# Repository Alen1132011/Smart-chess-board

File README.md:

# Smart Chess Board

A physical chess board that can detect the position of chess pieces in real time using Hall effect sensors and provide visual feedback through RGB LEDs.

The project combines custom electronics, firmware and a 3D printed enclosure to create a chess board that can understand what is happening on the board without using mechanical switches.

## Budget & SMT Notes

- **Shipping:** Selected the cheapest available shipping method to Bosnia and Herzegovina ($71.75).
- **SMT Assembly:** I attempted to use Economic SMT Assembly to minimize costs, but JLCPCB automatically forces a switch to **Standard SMT Assembly** when incorporating WS2812B addressable LEDs.
- **Self-Funded Components:** To keep the requested grant minimal, I will personally cover all additional hardware costs (ESP32 controller board, magnets, and 3D printing materials for the enclosure).

## Current Status

The PCB design is complete and the first board is being prepared for production and assembly.

The project is still in development. Some features described below are planned and will be added as the hardware and firmware develop.

Once I assemble and test the first board, I will add more information to this repository, including photos, test results and a much more detailed assembly guide.

## Features

* Real-time piece detection using Hall effect sensors
* 128 Hall effect sensors
* RGB lighting under the chess squares
* Custom PCB designed specifically for the board
* Magnetic chess pieces using neodymium magnets
* Firmware developed for the board
* Planned Stockfish integration
* Planned connection to online chess platforms

## How It Works

Each chess piece has a small magnet in its base. Hall effect sensors placed underneath the board detect the magnetic field and determine whether a piece is present on a square.

The board uses 128 sensors connected through 74HC165 shift registers. This allows the microcontroller to read a large number of sensors without requiring a separate input pin for every sensor.

RGB LEDs are placed underneath the squares and can be used to show things such as possible moves, selected pieces, warnings and other information.

The main idea is to keep the playing surface completely clean while putting all of the electronics underneath it.

## Hardware

The main components currently used in the design are:

* Custom PCB designed in KiCad
* 128x HAL2041SO Hall effect sensors
* 16x 74HC165 shift registers
* SK6812 / WS2812B RGB LEDs
* 100nF capacitors
* 10kΩ and 330Ω resistors
* Chess pieces with neodymium magnets

The exact components and values may change after the first prototype is assembled and tested.

## Repository Structure

```text
CAD/              3D models and enclosure design
Firmware/         Board firmware
PCB/              KiCad PCB design files
Production/       Manufacturing and production files
Smart chess board Additional project files
README.md         Project documentation
```

## Assembly

The first version of the board has not been fully assembled yet, so the complete assembly guide is not available at the moment.

After I build the first board, I will add a detailed guide covering:

* PCB assembly
* Hall sensor placement
* LED installation
* Wiring and power
* Magnet placement in the chess pieces
* Firmware installation
* Initial testing and calibration
* Common problems and fixes

I want the guide to be based on the actual first build rather than documenting steps that have not been tested yet.

## Future Plans

The project is still being developed, and more features will be added after the first working board is finished.

Some of the planned improvements include:

* Stockfish integration
* Better move detection and validation
* More RGB lighting effects
* Online chess integration
* Calibration tools
* Improved enclosure
* More detailed documentation

The first assembled board will be an important milestone because it will show which parts of the current design work as expected and which parts need to be improved.

## Libraries and Tools

* KiCad
* PlatformIO
* FastLED
* Stockfish
  
 ## Project Renders & Schematics

## Project Status

PCB design: Complete
CAD design: In progress
Firmware: In progress
First board assembly: Upcoming
Detailed assembly guide: Coming after the first build

This project is being developed step by step. The documentation will be updated as the physical board is built, tested and improved.

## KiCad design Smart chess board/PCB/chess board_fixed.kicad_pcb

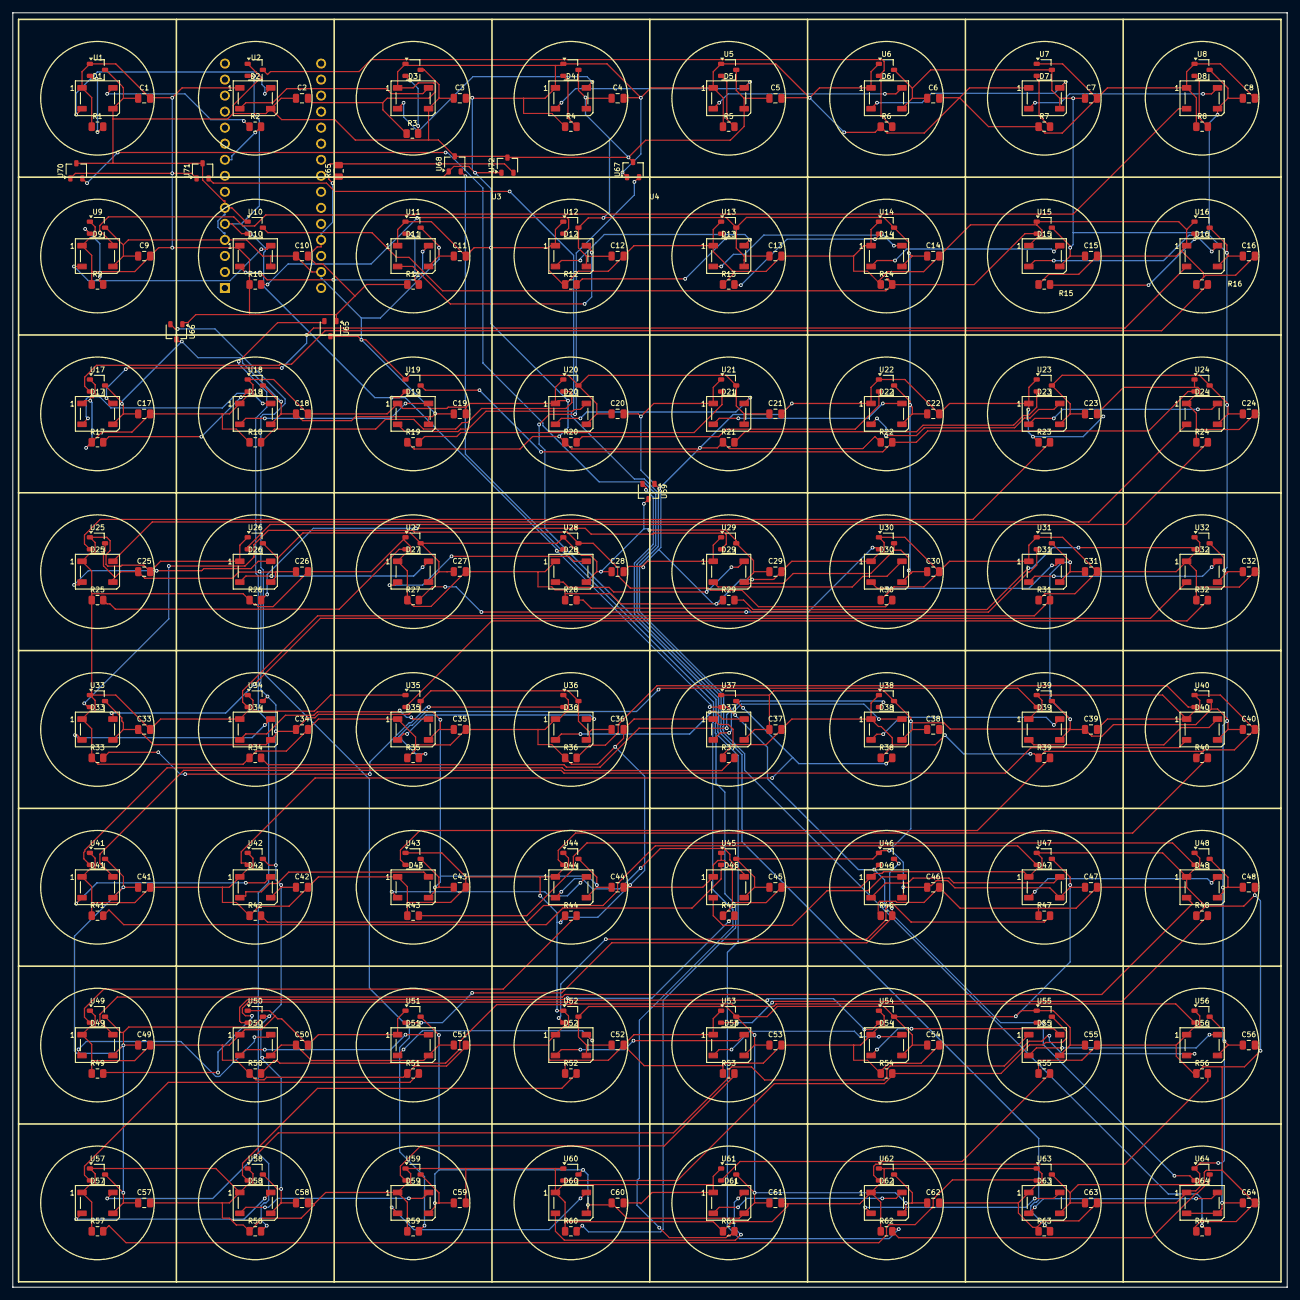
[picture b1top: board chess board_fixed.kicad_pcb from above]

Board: 2 copper layers, 201.9 x 201.9 mm, 266 parts (1 on the bottom side), 132 nets.

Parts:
A1: Arduino_Nano_Every; Arduino_Nano
C1, C2, C3, C4, C5, C6, C7, C8, C9, C10, C11, C12, C13, C14, C15, C16, C17, C18, C19, C20, C21, C22, C23, C24, C25, C26, C27, C28, C29, C30, C31, C32, C33, C34, C35, C36, C37, C38, C39, C40, C41, C42, C43, C44, C45, C46, C47, C48, C49, C50, C51, C52, C53, C54, C55, C56, C57, C58, C59, C60, C61, C62, C63, C64: 100nF; C_0805_2012Metric
D1, D2, D3, D4, D5, D6, D7, D8, D9, D10, D11, D12, D13, D14, D15, D16, D17, D18, D19, D20, D21, D22, D23, D24, D25, D26, D27, D28, D29, D30, D31, D32, D33, D34, D35, D36, D37, D38, D39, D40, D41, D42, D43, D44, D45, D46, D47, D48, D49, D50, D51, D52, D53, D54, D55, D56, D57, D58, D59, D60, D61, D62, D63, D64: WS2812B; LED_WS2812B_PLCC4_5.0x5.0mm_P3.2mm
R1, R3, R4, R5, R6, R7, R8, R9, R10, R11, R12, R13, R14, R15, R16, R17, R18, R19, R20, R21, R22, R23, R24, R25, R26, R27, R28, R29, R30, R31, R32, R33, R34, R35, R36, R37, R38, R39, R40, R41, R42, R43, R44, R45, R46, R47, R48, R49, R50, R51, R52, R53, R54, R55, R56, R57, R58, R59, R60, R61, R62, R63, R64, R65: 10k; R_0805_2012Metric
R2: 330Ω; R_0805_2012Metric
U1, U3, U4, U5, U6, U7, U8, U9, U11, U12, U13, U14, U15, U16, U17, U18, U20, U21, U22, U23, U24, U25, U26, U27, U29, U30, U31, U32, U33, U34, U35, U36, U38, U39, U40, U41, U42, U43, U44, U45, U47, U48, U49, U50, U51, U52, U53, U54, U56, U57, U58, U59, U60, U61, U62, U63, U65, U66, U67, U68, U69, U70, U71, U72: A1104xLH; SOT-23W
U2, U10, U19, U28, U37, U46, U55, U64: 74HC165; SOT-23W

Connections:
+5V: A1.27 (+5V), C1.2, C2.2, C3.2, C4.2, C5.2, C6.2, C7.2, C8.2, C9.2, C10.2, C11.2, C12.2, C13.2, C14.2, C15.2, C16.2, C17.2, C18.2, C19.2, C20.2, C21.2, C22.2, C23.2, C24.2, C25.2, C26.2, C27.2, C28.2, C29.2, C30.2, C31.2, C32.2, C33.2, C34.2, C35.2, C36.2, C37.2, C38.2, C39.2, C40.2, C41.2, C42.2, C43.2, C44.2, C45.2, C46.2, C47.2, C48.2, C49.2, C50.2, C51.2, C52.2, C53.2, C54.2, C55.2, C56.2, C57.2, C58.2, C59.2, C60.2, C61.2, C62.2, C63.2, C64.2, D1.1 (VDD), D2.1 (VDD), D3.1 (VDD), D4.1 (VDD), D5.1 (VDD), D6.1 (VDD), D7.1 (VDD), D8.1 (VDD), D9.1 (VDD), D10.1 (VDD), D11.1 (VDD), D12.1 (VDD), D13.1 (VDD), D14.1 (VDD), D15.1 (VDD), D16.1 (VDD), D17.1 (VDD), D18.1 (VDD), D19.1 (VDD), D20.1 (VDD), D21.1 (VDD), D22.1 (VDD), D23.1 (VDD), D24.1 (VDD), D25.1 (VDD), D26.1 (VDD), D27.1 (VDD), D28.1 (VDD), D29.1 (VDD), D30.1 (VDD), D31.1 (VDD), D32.1 (VDD), D33.1 (VDD), D34.1 (VDD), D35.1 (VDD), D36.1 (VDD), D37.1 (VDD), D38.1 (VDD), D39.1 (VDD), D40.1 (VDD), D41.1 (VDD), D42.1 (VDD), D43.1 (VDD), D44.1 (VDD), D45.1 (VDD), D46.1 (VDD), D47.1 (VDD), D48.1 (VDD), D49.1 (VDD), D50.1 (VDD), D51.1 (VDD), D52.1 (VDD), D53.1 (VDD), D54.1 (VDD), D55.1 (VDD), D56.1 (VDD), D57.1 (VDD), D58.1 (VDD), D59.1 (VDD), D60.1 (VDD), D61.1 (VDD), D62.1 (VDD), D63.1 (VDD), D64.1 (VDD), R1.1, R3.1, R4.1, R5.1, R6.1, R7.1, R8.1, R9.1, R10.1, R11.1, R12.1, R13.1, R14.1, R15.1, R16.1, R17.1, R18.1, R19.1, R20.1, R21.1, R22.1, R23.1, R24.1, R25.1, R26.1, R27.1, R28.1, R29.1, R30.1, R31.1, R32.1, R33.1, R34.1, R35.1, R36.1, R37.1, R38.1, R39.1, R40.1, R41.1, R42.1, R43.1, R44.1, R45.1, R46.1, R47.1, R48.1, R49.1, R50.1, R51.1, R52.1, R53.1, R54.1, R55.1, R56.1, R57.1, R58.1, R59.1, R60.1, R61.1, R62.1, R63.1, R64.1, R65.1, U1.1 (V_{CC}), U3.1 (V_{CC}), U4.1 (V_{CC}), U5.1 (V_{CC}), U6.1 (V_{CC}), U7.1 (V_{CC}), U8.1 (V_{CC}), U9.1 (V_{CC}), U11.1 (V_{CC}), U12.1 (V_{CC}), U13.1 (V_{CC}), U14.1 (V_{CC}), U15.1 (V_{CC}), U16.1 (V_{CC}), U17.1 (V_{CC}), U18.1 (V_{CC}), U20.1 (V_{CC}), U21.1 (V_{CC}), U22.1 (V_{CC}), U23.1 (V_{CC}), U24.1 (V_{CC}), U25.1 (V_{CC}), U26.1 (V_{CC}), U27.1 (V_{CC}), U29.1 (V_{CC}), U30.1 (V_{CC}), U31.1 (V_{CC}), U32.1 (V_{CC}), U33.1 (V_{CC}), U34.1 (V_{CC}), U35.1 (V_{CC}), U36.1 (V_{CC}), U38.1 (V_{CC}), U39.1 (V_{CC}), U40.1 (V_{CC}), U41.1 (V_{CC}), U42.1 (V_{CC}), U43.1 (V_{CC}), U44.1 (V_{CC}), U45.1 (V_{CC}), U47.1 (V_{CC}), U48.1 (V_{CC}), U49.1 (V_{CC}), U50.1 (V_{CC}), U51.1 (V_{CC}), U52.1 (V_{CC}), U53.1 (V_{CC}), U54.1 (V_{CC}), U56.1 (V_{CC}), U57.1 (V_{CC}), U58.1 (V_{CC}), U59.1 (V_{CC}), U60.1 (V_{CC}), U61.1 (V_{CC}), U62.1 (V_{CC}), U63.1 (V_{CC}), U65.1 (V_{CC}), U66.1 (V_{CC}), U67.1 (V_{CC}), U68.1 (V_{CC}), U69.1 (V_{CC}), U70.1 (V_{CC}), U71.1 (V_{CC}), U72.1 (V_{CC})
/S0: R1.2, U1.2 (V_{OUT})
/S1: R3.2, U3.2 (V_{OUT})
/S2: R4.2, U4.2 (V_{OUT})
/S3: R5.2, U5.2 (V_{OUT})
/S4: R6.2, U2.3 (D4), U6.2 (V_{OUT})
/S5: R7.2, U7.2 (V_{OUT})
/S6: R8.2, U8.2 (V_{OUT})
/S7: R9.2, U9.2 (V_{OUT})
/S8: R11.2, U11.2 (V_{OUT})
/S9: R10.2, U12.2 (V_{OUT})
/S10: R12.2, U13.2 (V_{OUT})
/S11: R13.2, U14.2 (V_{OUT})
/S12: R14.2, U10.3 (D4), U15.2 (V_{OUT})
/S13: R15.2, U16.2 (V_{OUT})
/S14: R16.2, U17.2 (V_{OUT})
/S15: R17.2, U18.2 (V_{OUT})
/S16: R18.2, U20.2 (V_{OUT})
/S17: R19.2, U21.2 (V_{OUT})
/S18: R20.2, U22.2 (V_{OUT})
/S19: R21.2, U23.2 (V_{OUT})
/S20: R22.2, U19.3 (D4), U24.2 (V_{OUT})
/S21: R23.2, U25.2 (V_{OUT})
/S22: R24.2, U26.2 (V_{OUT})
/S23: R25.2, U27.2 (V_{OUT})
/S24: R26.2, U29.2 (V_{OUT})
/S25: R27.2, U30.2 (V_{OUT})
/S26: R28.2, U31.2 (V_{OUT})
/S27: R29.2, U32.2 (V_{OUT})
/S28: R30.2, U28.3 (D4), U33.2 (V_{OUT})
/S29: R31.2, U34.2 (V_{OUT})
/S30: R32.2, U35.2 (V_{OUT})
/S31: R33.2, U36.2 (V_{OUT})
/S32: R34.2, U38.2 (V_{OUT})
/S33: R35.2, U39.2 (V_{OUT})
/S34: R36.2, U40.2 (V_{OUT})
/S35: R37.2, U41.2 (V_{OUT})
/S36: R38.2, U37.3 (D4), U42.2 (V_{OUT})
/S37: R39.2, U43.2 (V_{OUT})
/S38: R40.2, U44.2 (V_{OUT})
/S39: R41.2, U45.2 (V_{OUT})
/S40: R42.2, U47.2 (V_{OUT})
/S41: R43.2, U48.2 (V_{OUT})
/S42: R44.2, U49.2 (V_{OUT})
/S43: R45.2, U50.2 (V_{OUT})
/S44: R46.2, U46.3 (D4), U51.2 (V_{OUT})
/S45: R47.2, U52.2 (V_{OUT})
/S46: R48.2, U53.2 (V_{OUT})
/S47: R49.2, U54.2 (V_{OUT})
/S48: R50.2, U56.2 (V_{OUT})
/S49: R51.2, U57.2 (V_{OUT})
/S50: R52.2, U58.2 (V_{OUT})
/S51: R53.2, U59.2 (V_{OUT})
/S52: R54.2, U55.3 (D4), U60.2 (V_{OUT})
/S53: R55.2, U61.2 (V_{OUT})
/S54: R56.2, U62.2 (V_{OUT})
/S55: R57.2, U63.2 (V_{OUT})
/S56: R58.2, U65.2 (V_{OUT})
/S57: R59.2, U66.2 (V_{OUT})
/S58: R60.2, U67.2 (V_{OUT})
/S59: R61.2, U68.2 (V_{OUT})
/S60: R62.2, U64.3 (D4), U69.2 (V_{OUT})
/S61: R63.2, U70.2 (V_{OUT})
/S62: R64.2, U71.2 (V_{OUT})
/S63: R65.2, U72.2 (V_{OUT})
GND: A1.4 (GND), A1.6 (D3), A1.29 (GND), C1.1, C2.1, C3.1, C4.1, C5.1, C6.1, C7.1, C8.1, C9.1, C10.1, C11.1, C12.1, C13.1, C14.1, C15.1, C16.1, C17.1, C18.1, C19.1, C20.1, C21.1, C22.1, C23.1, C24.1, C25.1, C26.1, C27.1, C28.1, C29.1, C30.1, C31.1, C32.1, C33.1, C34.1, C35.1, C36.1, C37.1, C38.1, C39.1, C40.1, C41.1, C42.1, C43.1, C44.1, C45.1, C46.1, C47.1, C48.1, C49.1, C50.1, C51.1, C52.1, C53.1, C54.1, C55.1, C56.1, C57.1, C58.1, C59.1, C60.1, C61.1, C62.1, C63.1, C64.1, D1.3 (VSS), D2.3 (VSS), D3.3 (VSS), D4.3 (VSS), D5.3 (VSS), D6.3 (VSS), D7.3 (VSS), D8.3 (VSS), D9.3 (VSS), D10.3 (VSS), D11.3 (VSS), D12.3 (VSS), D13.3 (VSS), D14.3 (VSS), D15.3 (VSS), D16.3 (VSS), D17.3 (VSS), D18.3 (VSS), D19.3 (VSS), D20.3 (VSS), D21.3 (VSS), D22.3 (VSS), D23.3 (VSS), D24.3 (VSS), D25.3 (VSS), D26.3 (VSS), D27.3 (VSS), D28.3 (VSS), D29.3 (VSS), D30.3 (VSS), D31.3 (VSS), D32.3 (VSS), D33.3 (VSS), D34.3 (VSS), D35.3 (VSS), D36.3 (VSS), D37.3 (VSS), D38.3 (VSS), D39.3 (VSS), D40.3 (VSS), D41.3 (VSS), D42.3 (VSS), D43.3 (VSS), D44.3 (VSS), D45.3 (VSS), D46.3 (VSS), D47.3 (VSS), D48.3 (VSS), D49.3 (VSS), D50.3 (VSS), D51.3 (VSS), D52.3 (VSS), D53.3 (VSS), D54.3 (VSS), D55.3 (VSS), D56.3 (VSS), D57.3 (VSS), D58.3 (VSS), D59.3 (VSS), D60.3 (VSS), D61.3 (VSS), D62.3 (VSS), D63.3 (VSS), D64.2 (DOUT), D64.3 (VSS), U1.3 (GND), U2.1 (~PL), U3.3 (GND), U4.3 (GND), U5.3 (GND), U6.3 (GND), U7.3 (GND), U8.3 (GND), U9.3 (GND), U10.1 (~PL), U11.3 (GND), U12.3 (GND), U13.3 (GND), U14.3 (GND), U15.3 (GND), U16.3 (GND), U17.3 (GND), U18.3 (GND), U19.1 (~PL), U20.3 (GND), U21.3 (GND), U22.3 (GND), U23.3 (GND), U24.3 (GND), U25.3 (GND), U26.3 (GND), U27.3 (GND), U28.1 (~PL), U29.3 (GND), U30.3 (GND), U31.3 (GND), U32.3 (GND), U33.3 (GND), U34.3 (GND), U35.3 (GND), U36.3 (GND), U37.1 (~PL), U38.3 (GND), U39.3 (GND), U40.3 (GND), U41.3 (GND), U42.3 (GND), U43.3 (GND), U44.3 (GND), U45.3 (GND), U46.1 (~PL), U47.3 (GND), U48.3 (GND), U49.3 (GND), U50.3 (GND), U51.3 (GND), U52.3 (GND), U53.3 (GND), U54.3 (GND), U55.1 (~PL), U56.3 (GND), U57.3 (GND), U58.3 (GND), U59.3 (GND), U60.3 (GND), U61.3 (GND), U62.3 (GND), U63.3 (GND), U64.1 (~PL), U65.3 (GND), U66.3 (GND), U67.3 (GND), U68.3 (GND), U69.3 (GND), U70.3 (GND), U71.3 (GND), U72.3 (GND)
unnamed: A1.5 (D2), U2.2 (CP), U10.2 (CP), U19.2 (CP), U28.2 (CP), U37.2 (CP), U46.2 (CP), U55.2 (CP), U64.2 (CP)
unnamed: A1.9 (D6), R2.2
unnamed: D1.4 (DIN), R2.1
unnamed: D1.2 (DOUT), D2.4 (DIN)
unnamed: D2.2 (DOUT), D3.4 (DIN)
unnamed: D3.2 (DOUT), D4.4 (DIN)
unnamed: D4.2 (DOUT), D5.4 (DIN)
unnamed: D5.2 (DOUT), D6.4 (DIN)
unnamed: D6.2 (DOUT), D7.4 (DIN)
unnamed: D7.2 (DOUT), D8.4 (DIN)
unnamed: D8.2 (DOUT), D9.4 (DIN)
unnamed: D9.2 (DOUT), D10.4 (DIN)
unnamed: D10.2 (DOUT), D11.4 (DIN)
unnamed: D11.2 (DOUT), D12.4 (DIN)
unnamed: D12.2 (DOUT), D13.4 (DIN)
unnamed: D13.2 (DOUT), D14.4 (DIN)
unnamed: D14.2 (DOUT), D15.4 (DIN)
unnamed: D15.2 (DOUT), D16.4 (DIN)
unnamed: D16.2 (DOUT), D17.4 (DIN)
unnamed: D17.2 (DOUT), D18.4 (DIN)
unnamed: D18.2 (DOUT), D19.4 (DIN)
unnamed: D19.2 (DOUT), D20.4 (DIN)
unnamed: D20.2 (DOUT), D21.4 (DIN)
unnamed: D21.2 (DOUT), D22.4 (DIN)
unnamed: D22.2 (DOUT), D23.4 (DIN)
unnamed: D23.2 (DOUT), D24.4 (DIN)
unnamed: D24.2 (DOUT), D25.4 (DIN)
unnamed: D25.2 (DOUT), D26.4 (DIN)
unnamed: D26.2 (DOUT), D27.4 (DIN)
unnamed: D27.2 (DOUT), D28.4 (DIN)
unnamed: D28.2 (DOUT), D29.4 (DIN)
unnamed: D29.2 (DOUT), D30.4 (DIN)
unnamed: D30.2 (DOUT), D31.4 (DIN)
unnamed: D31.2 (DOUT), D32.4 (DIN)
unnamed: D32.2 (DOUT), D33.4 (DIN)
unnamed: D33.2 (DOUT), D34.4 (DIN)
unnamed: D34.2 (DOUT), D35.4 (DIN)
unnamed: D35.2 (DOUT), D36.4 (DIN)
unnamed: D36.2 (DOUT), D37.4 (DIN)
unnamed: D37.2 (DOUT), D38.4 (DIN)
unnamed: D38.2 (DOUT), D39.4 (DIN)
unnamed: D39.2 (DOUT), D40.4 (DIN)
unnamed: D40.2 (DOUT), D41.4 (DIN)
unnamed: D41.2 (DOUT), D42.4 (DIN)
unnamed: D42.2 (DOUT), D43.4 (DIN)
unnamed: D43.2 (DOUT), D44.4 (DIN)
unnamed: D44.2 (DOUT), D45.4 (DIN)
unnamed: D45.2 (DOUT), D46.4 (DIN)
unnamed: D46.2 (DOUT), D47.4 (DIN)
unnamed: D47.2 (DOUT), D48.4 (DIN)
unnamed: D48.2 (DOUT), D49.4 (DIN)
unnamed: D49.2 (DOUT), D50.4 (DIN)
unnamed: D50.2 (DOUT), D51.4 (DIN)
unnamed: D51.2 (DOUT), D52.4 (DIN)
unnamed: D52.2 (DOUT), D53.4 (DIN)
unnamed: D53.2 (DOUT), D54.4 (DIN)
unnamed: D54.2 (DOUT), D55.4 (DIN)
unnamed: D55.2 (DOUT), D56.4 (DIN)
unnamed: D56.2 (DOUT), D57.4 (DIN)
unnamed: D57.2 (DOUT), D58.4 (DIN)
unnamed: D58.2 (DOUT), D59.4 (DIN)
unnamed: D59.2 (DOUT), D60.4 (DIN)
unnamed: D60.2 (DOUT), D61.4 (DIN)
unnamed: D61.2 (DOUT), D62.4 (DIN)
unnamed: D62.2 (DOUT), D63.4 (DIN)
unnamed: D63.2 (DOUT), D64.4 (DIN)
